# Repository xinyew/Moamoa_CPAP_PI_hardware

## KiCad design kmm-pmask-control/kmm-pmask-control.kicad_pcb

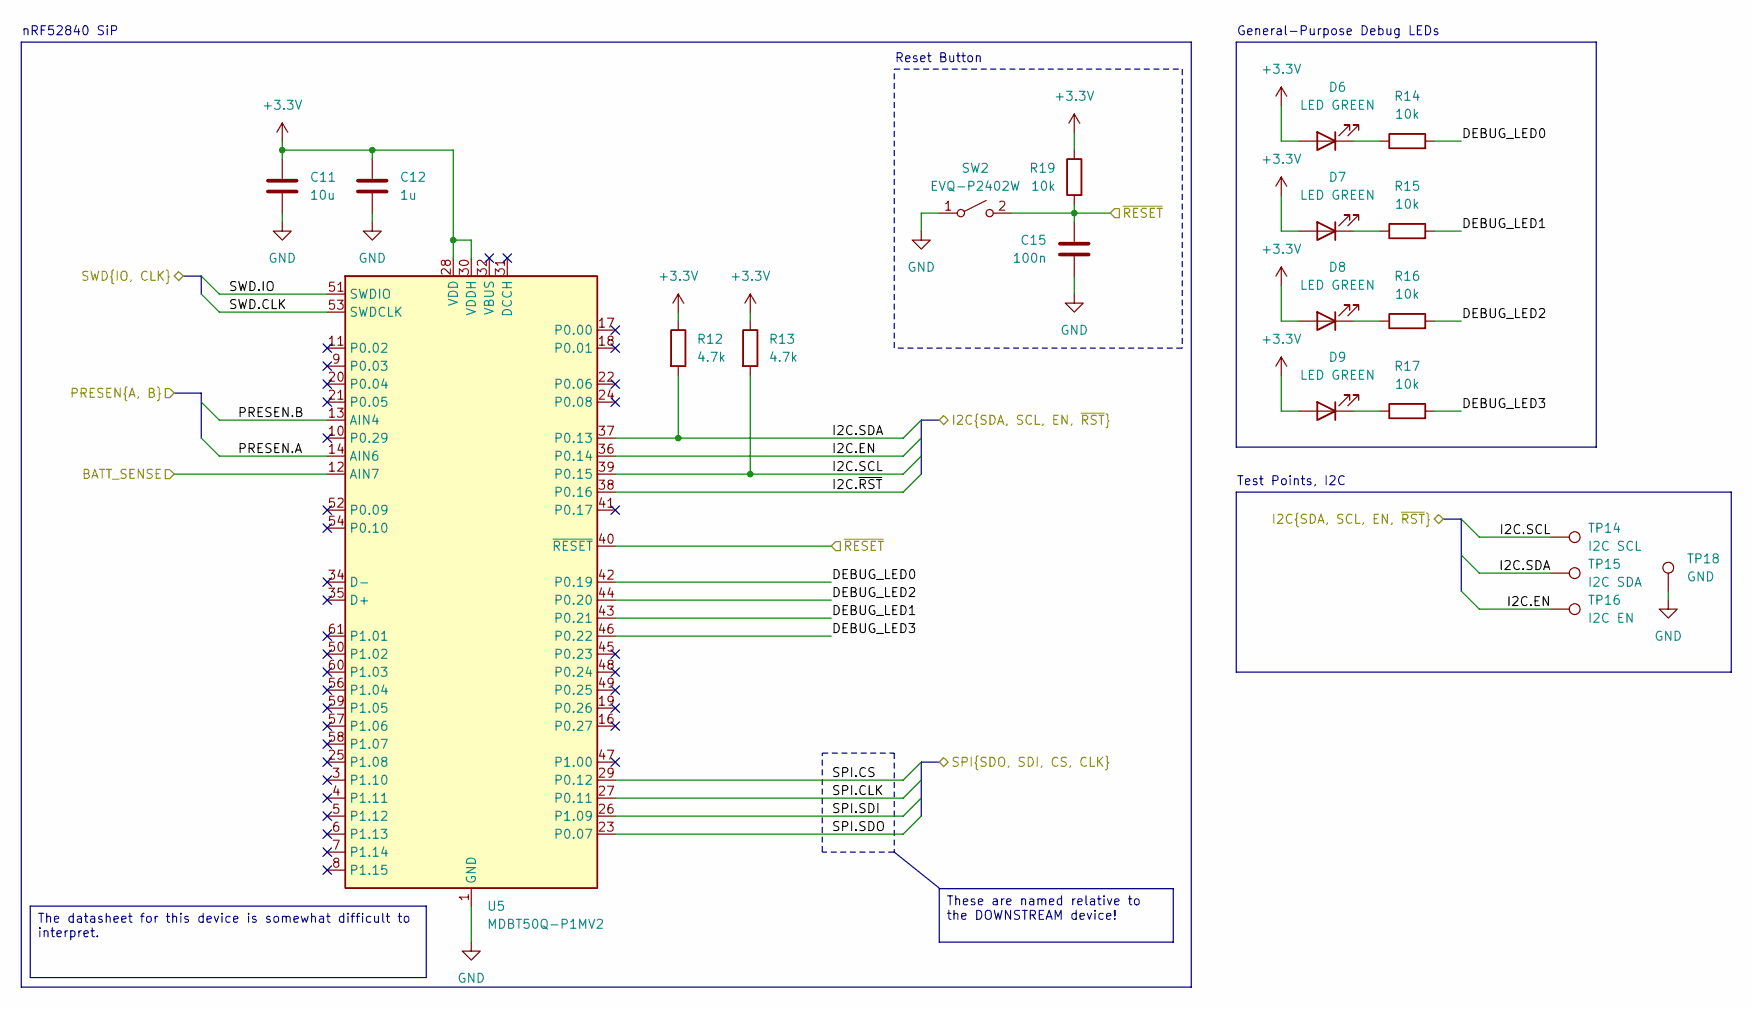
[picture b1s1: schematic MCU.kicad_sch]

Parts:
C11: 10u; C_0603_1608Metric_Pad1.08x0.95mm_HandSolder
C12: 1u; C_0402_1005Metric_Pad0.74x0.62mm_HandSolder
C15: 100n; C_0402_1005Metric_Pad0.74x0.62mm_HandSolder
D6, D7, D8, D9: LED GREEN; LED_0603_1608Metric_Pad1.05x0.95mm_HandSolder; Manufacturer P/N LTST-C190GKT
R12, R13: 4.7k; R_0402_1005Metric_Pad0.72x0.64mm_HandSolder
R14, R15, R16, R17, R19: 10k; R_0402_1005Metric_Pad0.72x0.64mm_HandSolder
SW2: EVQ-P2402W; SW_SPST_EVQP2_ShortPushTravel_H2.5mm; Manufacturer P/N EVQ-P2402W
TP14: I2C SCL; TestPoint_Pad_D1.0mm
TP15: I2C SDA; TestPoint_Pad_D1.0mm
TP16: I2C EN; TestPoint_Pad_D1.0mm
TP18: GND; TestPoint_Pad_D1.0mm
U5: MDBT50Q-P1MV2; Raytac_MDBT50Q; Manufacturer P/N MDBT50Q-P1MV2

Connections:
+3.3V: C11.1, C12.1, D6.2 (A), D7.2 (A), D8.2 (A), D9.2 (A), R12.1, R13.1, R19.1, U5.28 (VDD), U5.30 (VDDH); also elsewhere on the board
/Board Perhipherals/SPI.CLK: U5.27 (P0.11); also elsewhere on the board
/Board Perhipherals/SPI.CS: U5.29 (P0.12); also elsewhere on the board
/Board Perhipherals/SPI.SDI: U5.26 (P1.09); also elsewhere on the board
/Board Perhipherals/SPI.SDO: U5.23 (P0.07); also elsewhere on the board
/Board Perhipherals/SWD.CLK: U5.53 (SWDCLK); also elsewhere on the board
/Board Perhipherals/SWD.IO: U5.51 (SWDIO); also elsewhere on the board
/Board Perhipherals/~RESET: C15.1, R19.2, SW2.2 (B), U5.40 (~RESET); also elsewhere on the board
/MCU/BATT_SENSE: U5.12 (AIN7); also elsewhere on the board
/MCU/DEBUG_LED0: R14.2, U5.42 (P0.19)
/MCU/DEBUG_LED1: R15.2, U5.43 (P0.21)
/MCU/DEBUG_LED2: R16.2, U5.44 (P0.20)
/MCU/DEBUG_LED3: R17.2, U5.46 (P0.22)
/MCU/I2C.EN: TP16.1 (1_1), U5.36 (P0.14); also elsewhere on the board
/MCU/I2C.SCL: R13.2, TP14.1 (1_1), U5.39 (P0.15); also elsewhere on the board
/MCU/I2C.SDA: R12.2, TP15.1 (1_1), U5.37 (P0.13); also elsewhere on the board
/MCU/I2C.~RST: U5.38 (P0.16); also elsewhere on the board
/MCU/PRESEN.A: U5.14 (AIN6); also elsewhere on the board
/MCU/PRESEN.B: U5.13 (AIN4); also elsewhere on the board
GND: C11.2, C12.2, C15.2, SW2.1 (A), TP18.1 (1_1), U5.1 (GND), U5.2 (GND), U5.15 (GND), U5.33 (GND), U5.55 (GND); also elsewhere on the board
unnamed: D6.1 (K), R14.1
unnamed: D7.1 (K), R15.1
unnamed: D8.1 (K), R16.1
unnamed: D9.1 (K), R17.1

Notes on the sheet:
nRF52840 SiP
Reset Button
General-Purpose Debug LEDs
Test Points, I2C
The datasheet for this device is somewhat difficult to interpret.
These are named relative to the DOWNSTREAM device!

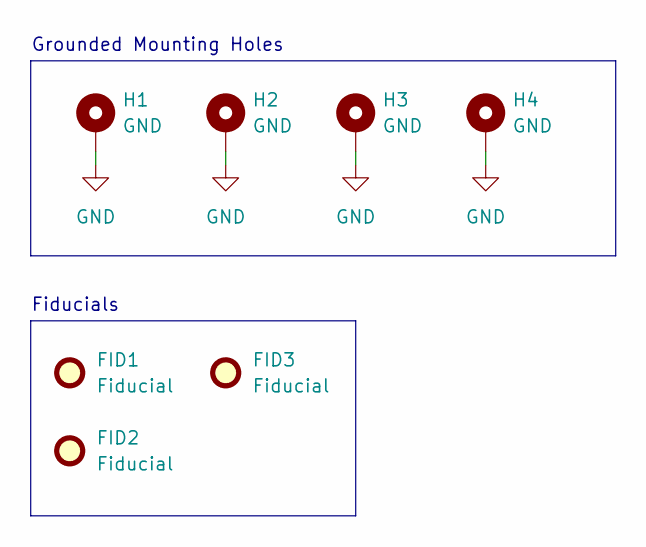
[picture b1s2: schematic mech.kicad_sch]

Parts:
FID1, FID2, FID3: Fiducial; Fiducial_1mm_Mask3mm
H1, H2, H3, H4: GND; MountingHole_3.2mm_M3_Pad

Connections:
GND: H1.1 (1_1), H2.1 (1_1), H3.1 (1_1), H4.1 (1_1); also elsewhere on the board

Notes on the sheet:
Grounded Mounting Holes
Fiducials

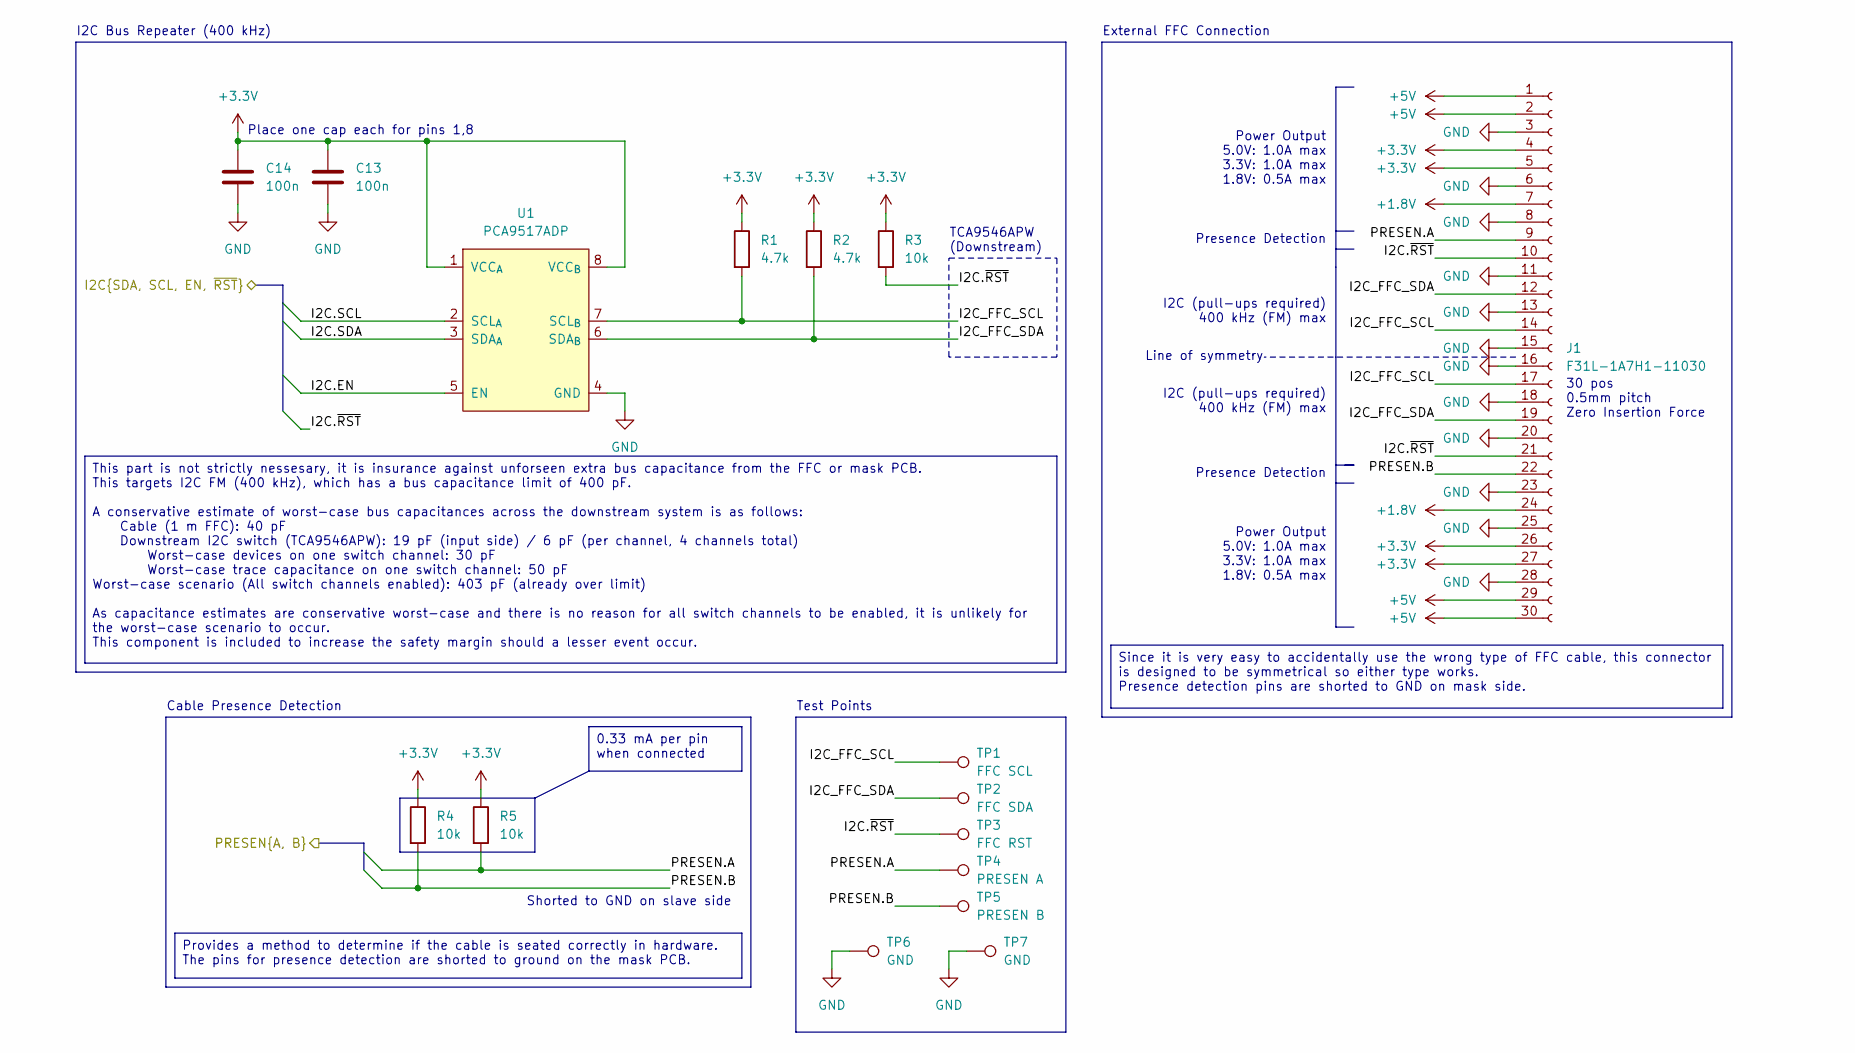
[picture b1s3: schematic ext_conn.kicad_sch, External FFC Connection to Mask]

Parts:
C13, C14: 100n; C_0402_1005Metric_Pad0.74x0.62mm_HandSolder
J1: F31L-1A7H1-11030; AMPHENOL_F31L-1A7H1-11030; Manufacturer P/N F31L-1A7H1-11030
R1, R2: 4.7k; R_0402_1005Metric_Pad0.72x0.64mm_HandSolder
R3, R4, R5: 10k; R_0402_1005Metric_Pad0.72x0.64mm_HandSolder
TP1: FFC SCL; TestPoint_Pad_D1.0mm
TP2: FFC SDA; TestPoint_Pad_D1.0mm
TP3: FFC RST; TestPoint_Pad_D1.0mm
TP4: PRESEN A; TestPoint_Pad_D1.0mm
TP5: PRESEN B; TestPoint_Pad_D1.0mm
TP6, TP7: GND; TestPoint_Pad_D1.0mm
U1: PCA9517ADP; TSSOP-8_3x3mm_P0.65mm; Manufacturer P/N PCA9517ADP,118

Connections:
+1.8V: J1.7, J1.24; also elsewhere on the board
+3.3V: C13.1, C14.1, J1.4, J1.5, J1.26, J1.27, R1.1, R2.1, R3.1, R4.1, R5.1, U1.1 (VCC_{A}), U1.8 (VCC_{B}); also elsewhere on the board
+5V: J1.1, J1.2, J1.29, J1.30; also elsewhere on the board
/MCU/I2C.EN: U1.5 (EN); also elsewhere on the board
/MCU/I2C.SCL: U1.2 (SCL_{A}); also elsewhere on the board
/MCU/I2C.SDA: U1.3 (SDA_{A}); also elsewhere on the board
/MCU/I2C.~RST: J1.10, J1.21, R3.2, TP3.1 (1_1); also elsewhere on the board
/MCU/PRESEN.A: J1.9, R5.2, TP4.1 (1_1); also elsewhere on the board
/MCU/PRESEN.B: J1.22, R4.2, TP5.1 (1_1); also elsewhere on the board
/Mask Connection/I2C_FFC_SCL: J1.14, J1.17, R1.2, TP1.1 (1_1), U1.7 (SCL_{B})
/Mask Connection/I2C_FFC_SDA: J1.12, J1.19, R2.2, TP2.1 (1_1), U1.6 (SDA_{B})
GND: C13.2, C14.2, J1.3, J1.6, J1.8, J1.11, J1.13, J1.15, J1.16, J1.18, J1.20, J1.23, J1.25, J1.28, TP6.1 (1_1), TP7.1 (1_1), U1.4 (GND); also elsewhere on the board

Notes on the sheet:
Place one cap each for pins 1,8
Line of symmetry
30 pos 0.5mm pitch Zero Insertion Force
Power Output 5.0V: 1.0A max 3.3V: 1.0A max 1.8V: 0.5A max
I2C (pull-ups required) 400 kHz (FM) max
Shorted to GND on slave side
Cable Presence Detection
External FFC Connection
Presence Detection
Test Points
TCA9546APW (Downstream)
I2C Bus Repeater (400 kHz)
Since it is very easy to accidentally use the wrong type of FFC cable, this connector is designed to be symmetrical so either type works. Presence detection pins are shorted to GND on mask side.
0.33 mA per pin when connected
This part is not strictly nessesary, it is insurance against unforseen extra bus capacitance from the FFC or mask PCB. This targets I2C FM (400 kHz), which has a bus capacitance limit of 400 pF. A conservative estimate of worst-case bus capacitances across the downstream system is as follows: Cable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
Provides a method to determine if the cable is seated correctly in hardware. The pins for presence detection are shorted to ground on the mask PCB.

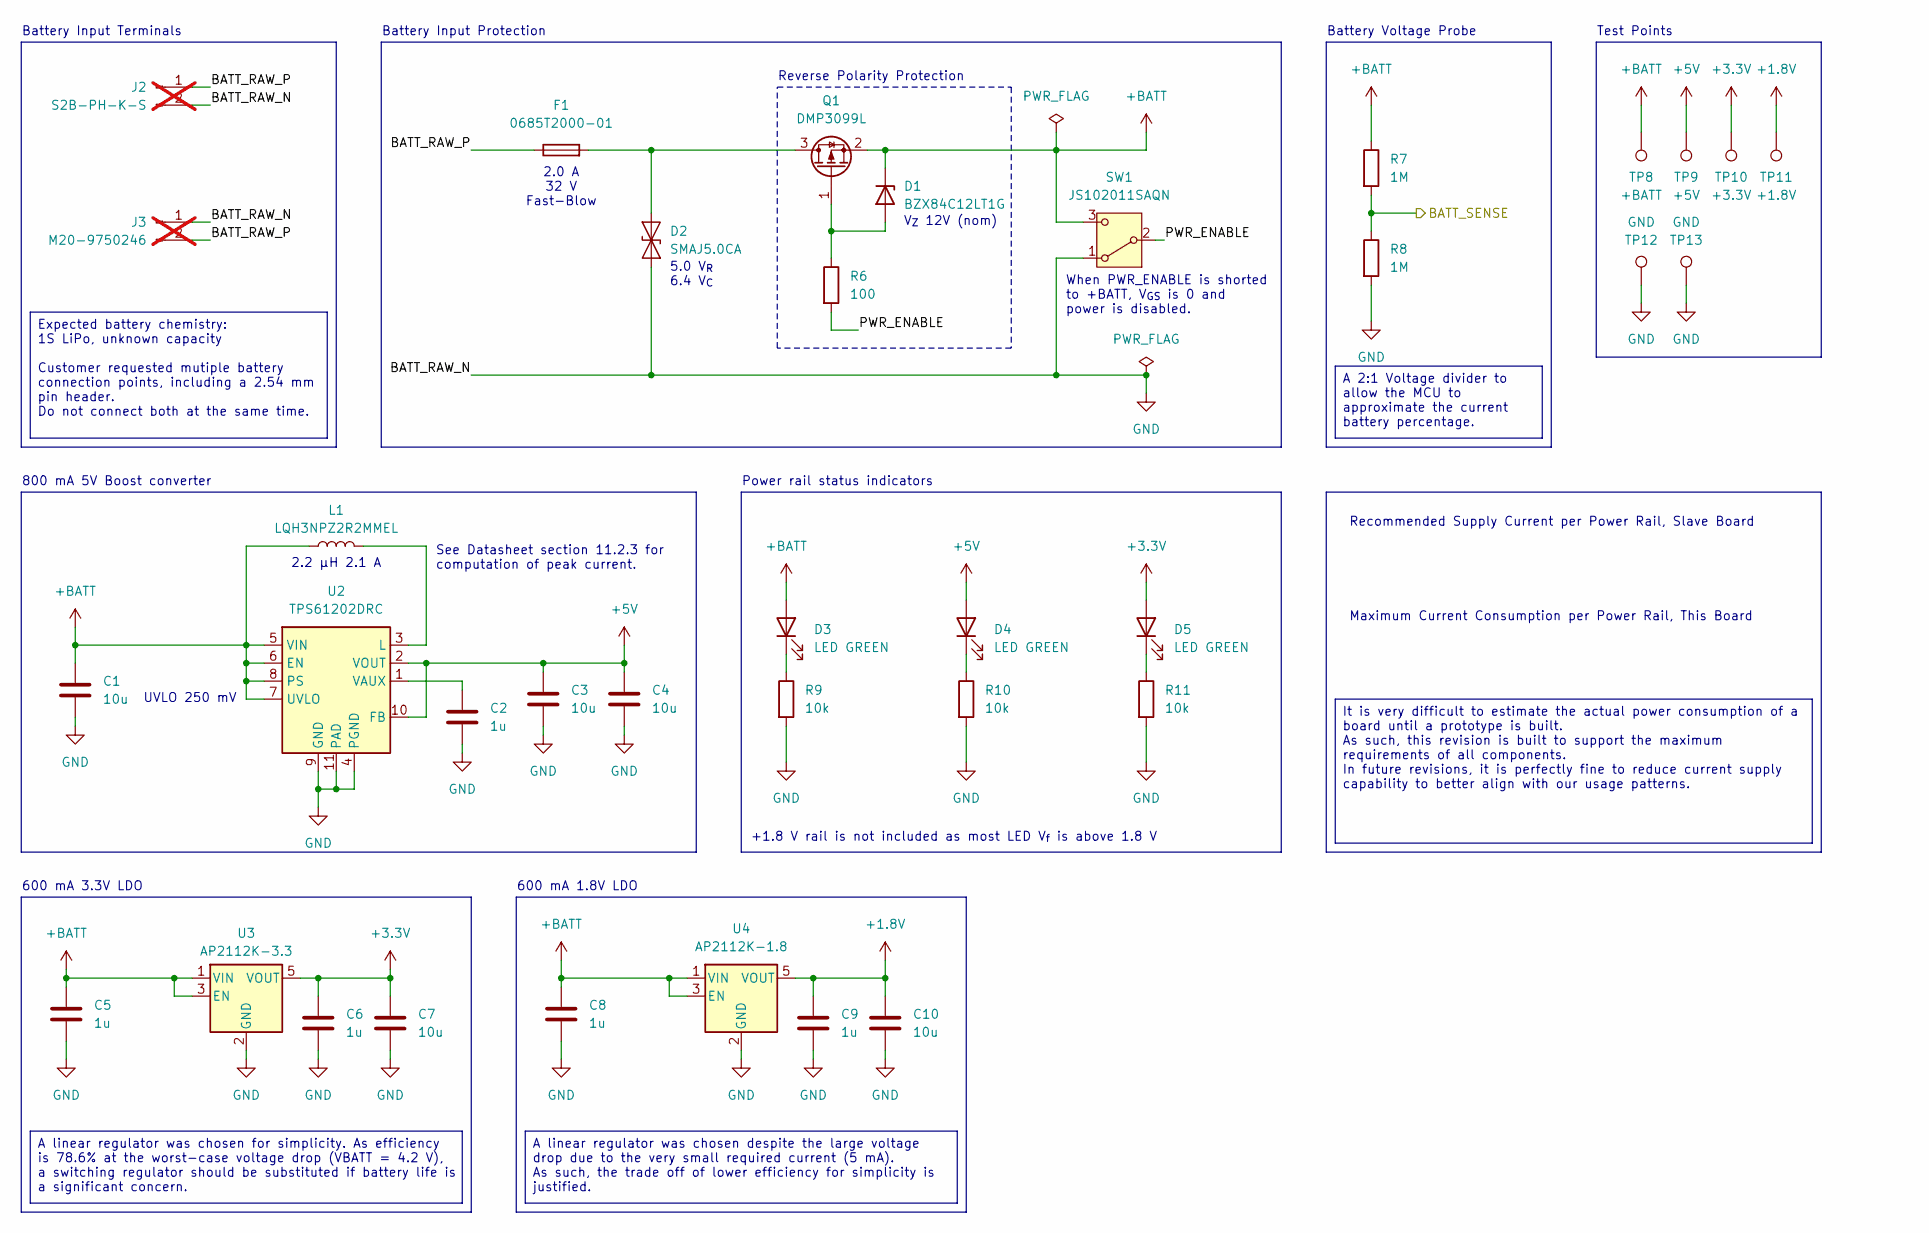
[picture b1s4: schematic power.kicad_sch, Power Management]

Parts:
C1, C3, C4, C7, C10: 10u; C_0603_1608Metric_Pad1.08x0.95mm_HandSolder
C2, C5, C6, C8, C9: 1u; C_0402_1005Metric_Pad0.74x0.62mm_HandSolder
D1: BZX84C12LT1G; SOT-23; Manufacturer P/N BZX84C12LT1G
D2: SMAJ5.0CA; D_SMA; Manufacturer P/N SMAJ5.0CA
D3, D4, D5: LED GREEN; LED_0603_1608Metric_Pad1.05x0.95mm_HandSolder; Manufacturer P/N LTST-C190GKT
F1: 0685T2000-01; Fuse_1206_3216Metric_Pad1.42x1.75mm_HandSolder; Manufacturer P/N 0685T2000-01
J2: S2B-PH-K-S; JST_PH_S2B-PH-K_1x02_P2.00mm_Horizontal; Manufacturer P/N S2B-PH-K-S; not fitted
J3: M20-9750246; PinHeader_1x02_P2.54mm_Horizontal; Manufacturer P/N M20-9750246; not fitted
L1: LQH3NPZ2R2MMEL; IND_LQH3NPZ2R2MMEL; Manufacturer P/N LQH3NPZ2R2MMEL
Q1: DMP3099L; SOT-23; Manufacturer P/N DMP3099L-13
R6: 100; R_0402_1005Metric_Pad0.72x0.64mm_HandSolder
R7, R8: 1M; R_0402_1005Metric_Pad0.72x0.64mm_HandSolder
R9, R10, R11: 10k; R_0402_1005Metric_Pad0.72x0.64mm_HandSolder
SW1: JS102011SAQN; SW_SPDT_CK_JS102011SAQN; Manufacturer P/N JS102011SAQN
TP8: +BATT; TestPoint_Pad_D1.0mm
TP9: +5V; TestPoint_Pad_D1.0mm
TP10: +3.3V; TestPoint_Pad_D1.0mm
TP11: +1.8V; TestPoint_Pad_D1.0mm
TP12, TP13: GND; TestPoint_Pad_D1.0mm
U2: TPS61202DRC; Texas_S-PVSON-N10_ThermalVias; Manufacturer P/N TPS61202DRCR
U3: AP2112K-3.3; SOT-23-5; Manufacturer P/N AP2112K-3.3TRG1
U4: AP2112K-1.8; SOT-23-5; Manufacturer P/N AP2112K-1.8TRG1

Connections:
+1.8V: C9.1, C10.1, TP11.1 (1_1), U4.5 (VOUT); also elsewhere on the board
+3.3V: C6.1, C7.1, D5.2 (A), TP10.1 (1_1), U3.5 (VOUT); also elsewhere on the board
+5V: C3.1, C4.1, D4.2 (A), TP9.1 (1_1), U2.2 (VOUT), U2.10 (FB); also elsewhere on the board
+BATT: C1.1, C5.1, C8.1, D1.3 (K), D3.2 (A), L1.1, Q1.2 (S), R7.1, SW1.3 (C), TP8.1 (1_1), U2.5 (VIN), U2.6 (EN), U2.7 (UVLO), U2.8 (PS), U3.1 (VIN), U3.3 (EN), U4.1 (VIN), U4.3 (EN)
/MCU/BATT_SENSE: R7.2, R8.1; also elsewhere on the board
/Power/BATT_RAW_P: F1.1, J2.1, J3.2
/Power/PWR_ENABLE: R6.2, SW1.2 (B)
GND: C1.2, C2.2, C3.2, C4.2, C5.2, C6.2, C7.2, C8.2, C9.2, C10.2, D2.1 (A1), J2.2, J3.1, R8.2, R9.2, R10.2, R11.2, SW1.1 (A), TP12.1 (1_1), TP13.1 (1_1), U2.4 (PGND), U2.9 (GND), U2.11 (PAD), U3.2 (GND), U4.2 (GND); also elsewhere on the board
unnamed: D1.1 (A), Q1.1 (G), R6.1
unnamed: D2.2 (A2), F1.2, Q1.3 (D)
unnamed: D3.1 (K), R9.1
unnamed: D4.1 (K), R10.1
unnamed: D5.1 (K), R11.1
unnamed: L1.2, U2.3 (L)
unnamed: C2.1, U2.1 (VAUX)

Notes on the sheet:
Battery Voltage Probe
Maximum Current Consumption per Power Rail, This Board
V_{Z} 12V (nom)
Power rail status indicators
600 mA 3.3V LDO
When PWR_ENABLE is shorted to +BATT, V_{GS} is 0 and power is disabled.
Reverse Polarity Protection
Test Points
600 mA 1.8V LDO
800 mA 5V Boost converter
+1.8 V rail is not included as most LED V_{f} is above 1.8 V
Battery Input Protection
Battery Input Terminals
2.0 A 32 V Fast-Blow
5.0 V_{R} 6.4 V_{C}
Recommended Supply Current per Power Rail, Slave Board
UVLO 250 mV
See Datasheet section 11.2.3 for computation of peak current.
2.2 µH 2.1 A
A linear regulator was chosen for simplicity. As efficiency is 78.6% at the worst-case voltage drop (VBATT = 4.2 V), a switching regulator should be substituted if battery life is a significant concern.
Expected battery chemistry: 1S LiPo, unknown capacity Customer requested mutiple battery connection points, including a 2.54 mm pin header. Do not connect both at the same time.
It is very difficult to estimate the actual power consumption of a board until a prototype is built. As such, this revision is built to support the maximum requirements of all components. In future revisions, it is perfectly fine to reduce current supply capability to better align with our usage pa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
A 2:1 Voltage divider to allow the MCU to approximate the current battery percentage.
A linear regulator was chosen despite the large voltage drop due to the very small required current (5 mA). As such, the trade off of lower efficiency for simplicity is justified.

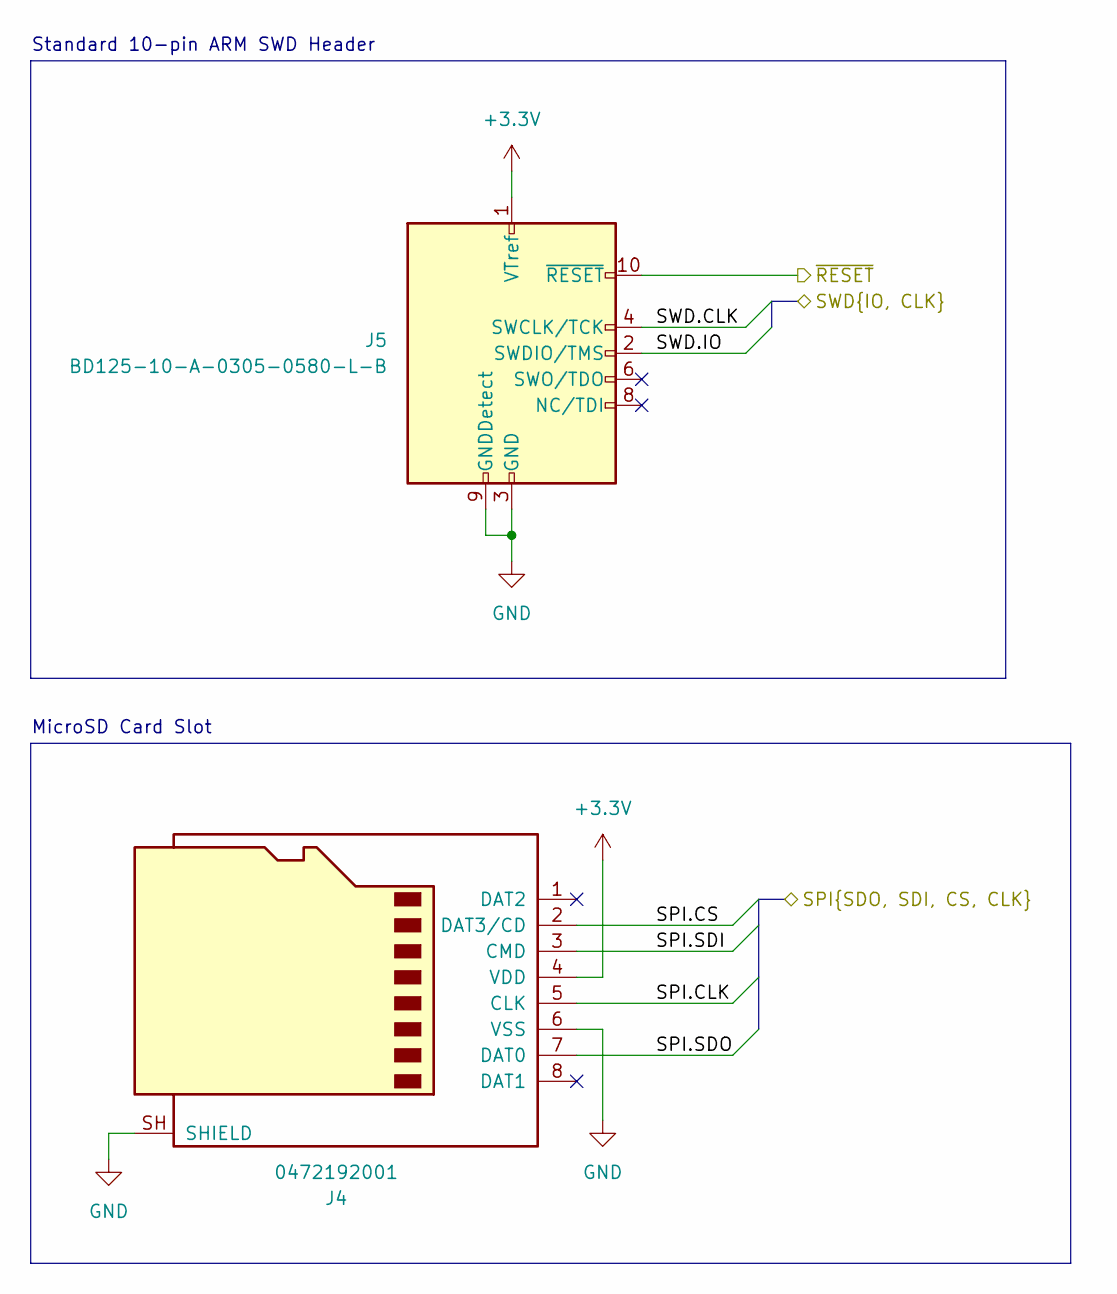
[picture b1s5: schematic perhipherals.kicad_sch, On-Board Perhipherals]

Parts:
J4: 0472192001; microSD_HC_Molex_47219-2001; Manufacturer P/N 0472192001
J5: BD125-10-A-0305-0580-L-B; PinHeader_2x05_P1.27mm_Vertical_SMD; Manufacturer P/N BD125-10-A-0305-0580-L-B

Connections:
+3.3V: J4.4 (VDD), J5.1 (VTref); also elsewhere on the board
/Board Perhipherals/SPI.CLK: J4.5 (CLK); also elsewhere on the board
/Board Perhipherals/SPI.CS: J4.2 (DAT3/CD); also elsewhere on the board
/Board Perhipherals/SPI.SDI: J4.3 (CMD); also elsewhere on the board
/Board Perhipherals/SPI.SDO: J4.7 (DAT0); also elsewhere on the board
/Board Perhipherals/SWD.CLK: J5.4 (SWCLK/TCK); also elsewhere on the board
/Board Perhipherals/SWD.IO: J5.2 (SWDIO/TMS); also elsewhere on the board
/Board Perhipherals/~RESET: J5.10 (~RESET); also elsewhere on the board
GND: J4.6 (VSS), J4.SH (SHIELD), J5.3 (GND), J5.5 (GND), J5.9 (GNDDetect); also elsewhere on the board

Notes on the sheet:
Standard 10-pin ARM SWD Header
MicroSD Card Slot

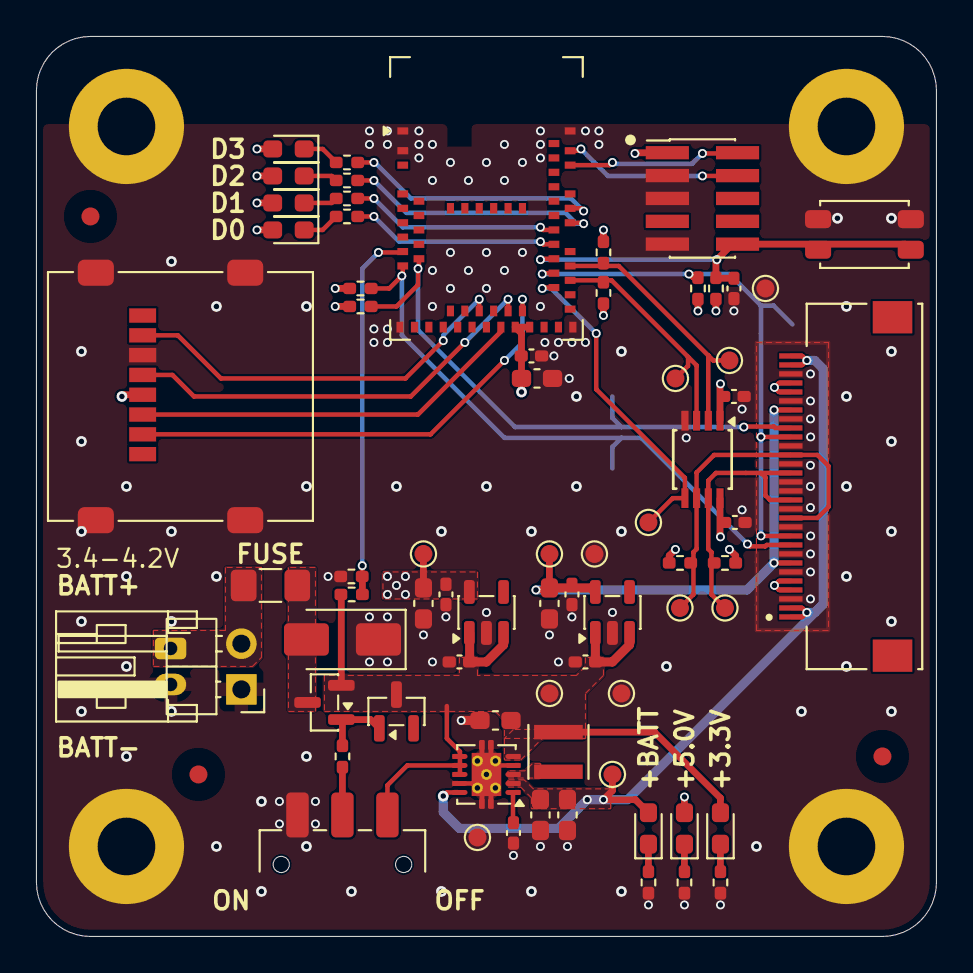
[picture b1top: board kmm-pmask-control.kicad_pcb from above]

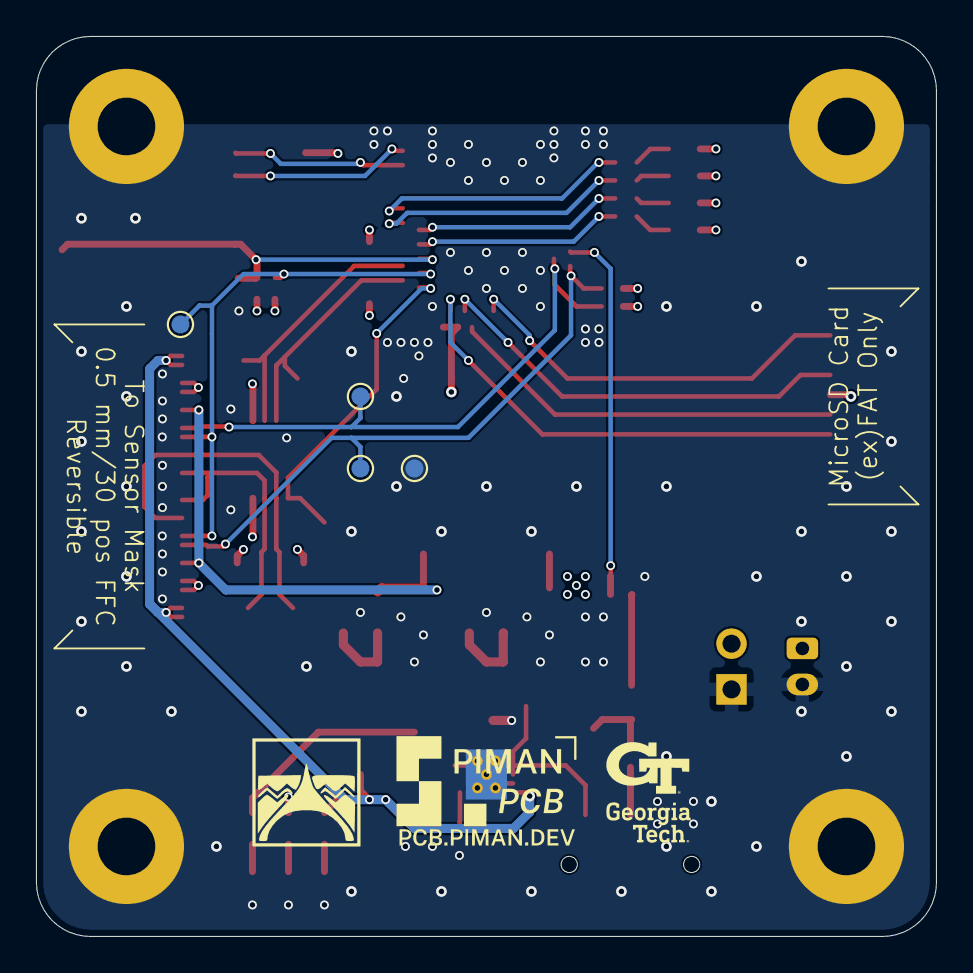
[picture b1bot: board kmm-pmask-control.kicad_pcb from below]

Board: 4 copper layers, 50.0 x 50.0 mm, 81 parts (4 on the bottom side), 38 nets.

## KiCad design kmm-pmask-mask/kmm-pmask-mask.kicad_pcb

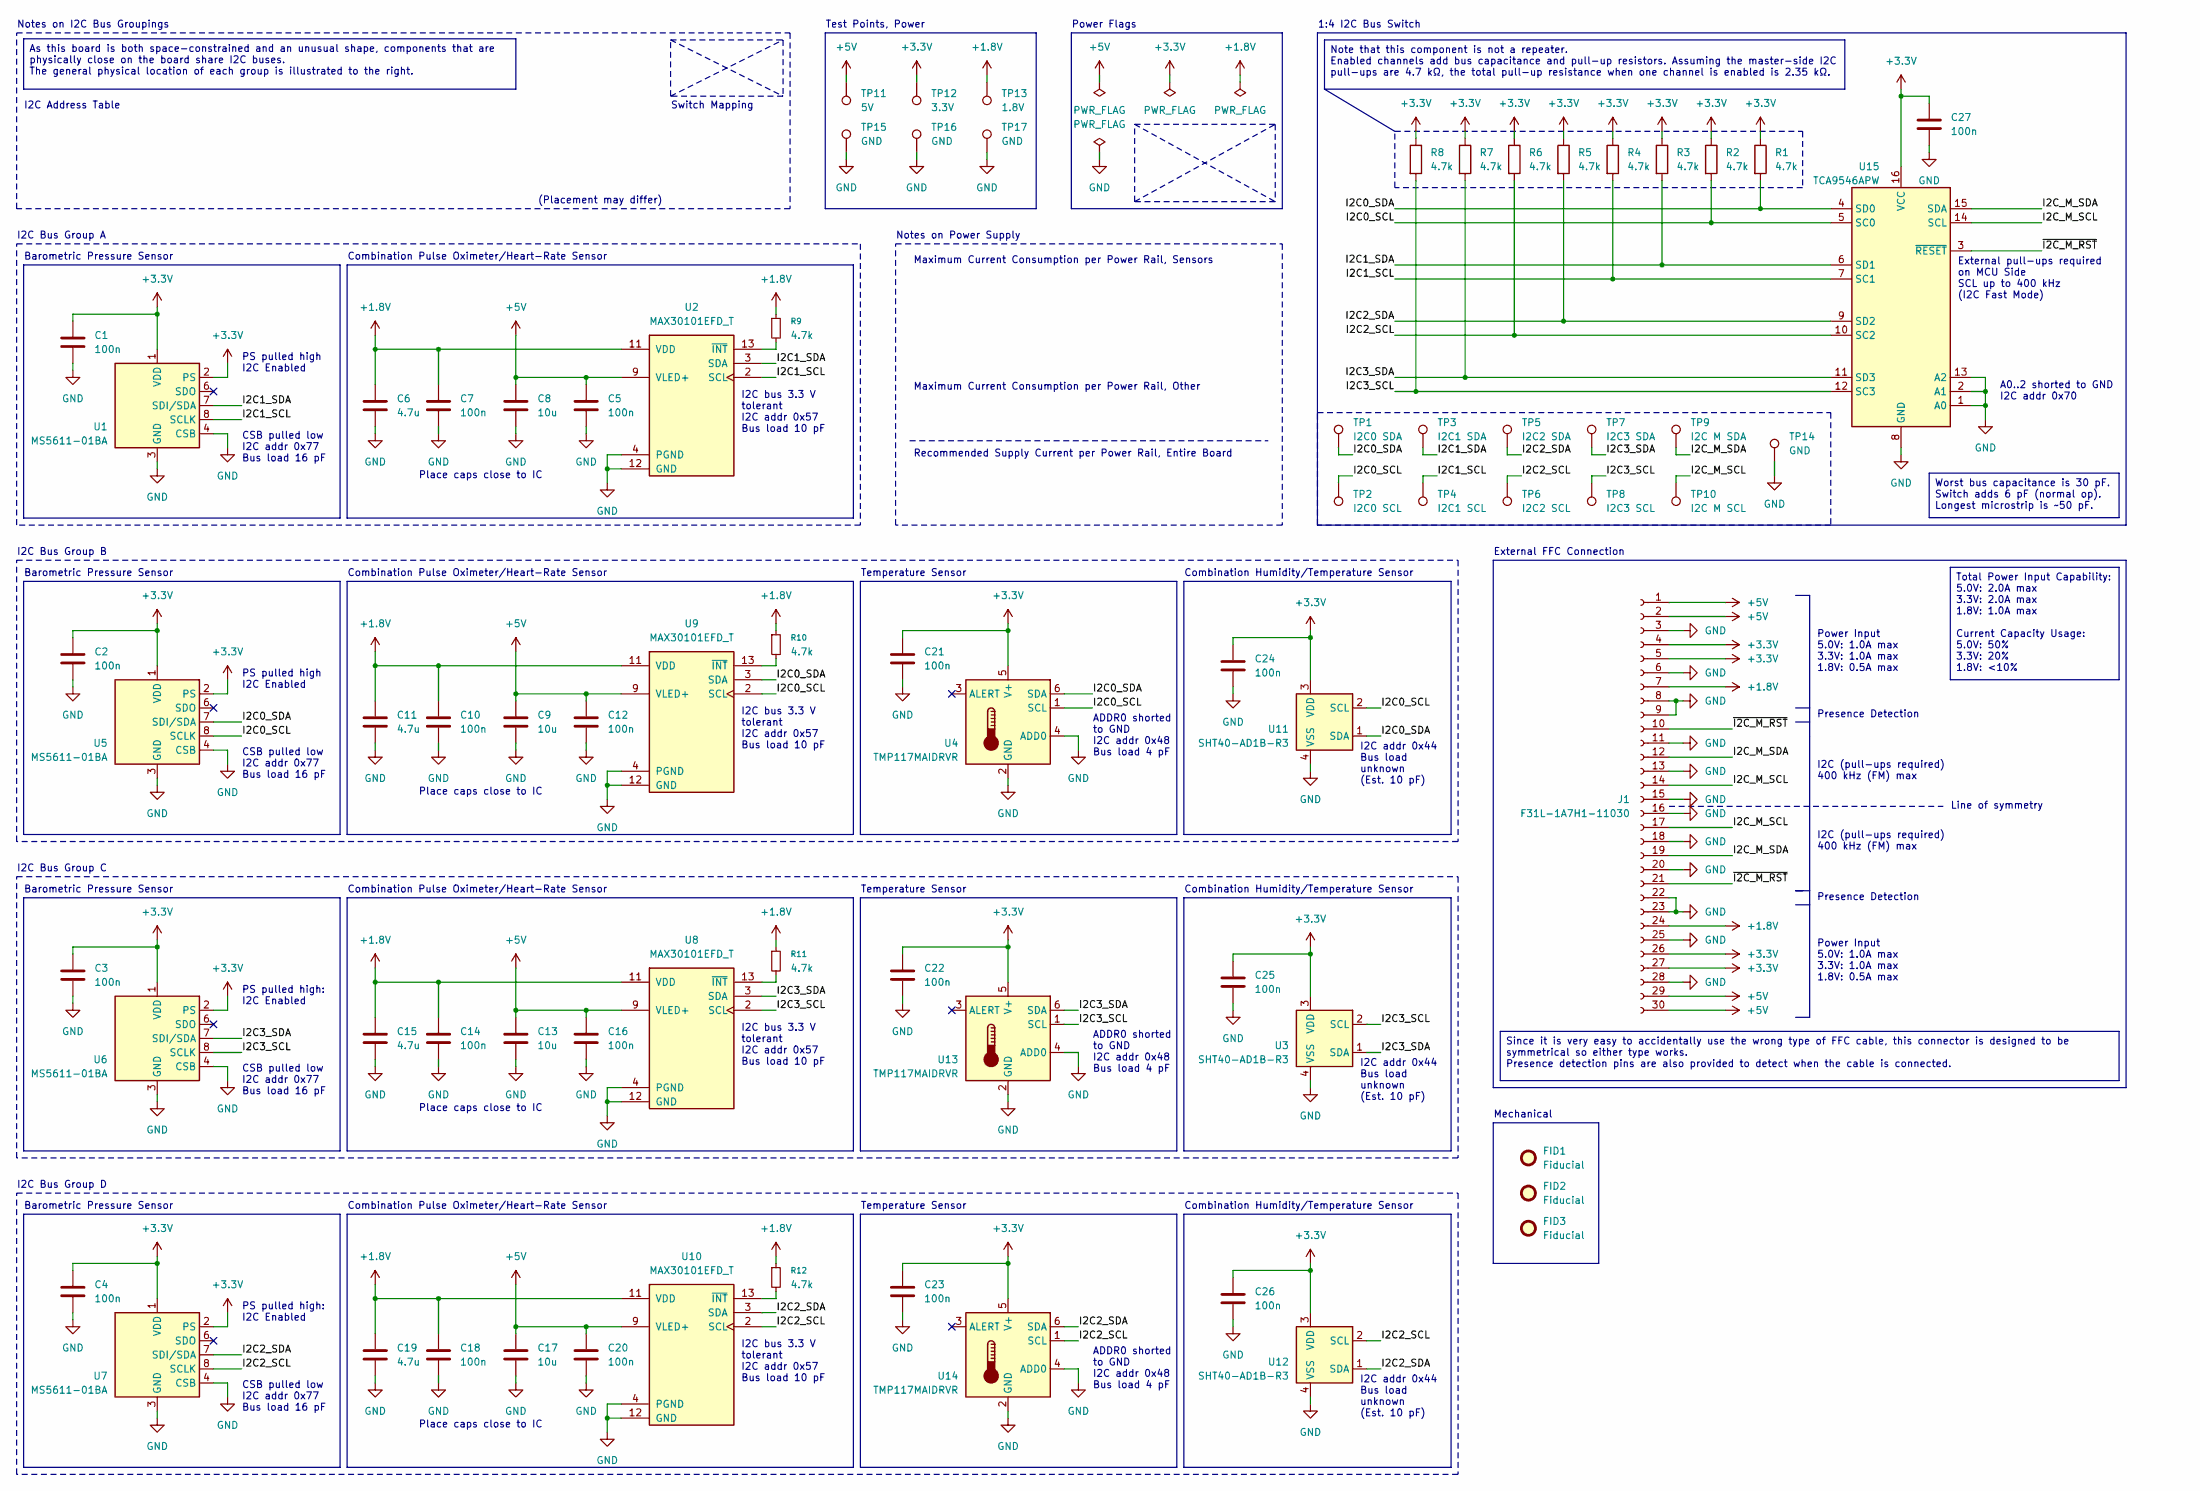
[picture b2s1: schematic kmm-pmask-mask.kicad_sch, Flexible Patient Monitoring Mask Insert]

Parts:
C1, C2, C3, C4, C5, C7, C10, C12, C14, C16, C18, C20, C21, C22, C23, C24, C25, C26, C27: 100n; C_0201_0603Metric_Pad0.64x0.40mm_HandSolder
C6, C11, C15, C19: 4.7u; C_0402_1005Metric_Pad0.74x0.62mm_HandSolder
C8, C9, C13, C17: 10u; C_0402_1005Metric_Pad0.74x0.62mm_HandSolder
FID1, FID2, FID3: Fiducial; Fiducial_1mm_Mask3mm
J1: F31L-1A7H1-11030; AMPHENOL_F31L-1A7H1-11030; Manufacturer P/N F31L-1A7H1-11030
R1, R2, R3, R4, R5, R6, R7, R8, R9, R10, R11, R12: 4.7k; R_0201_0603Metric_Pad0.64x0.40mm_HandSolder
TP1: I2C0 SDA; TestPoint_Pad_D1.0mm
TP2: I2C0 SCL; TestPoint_Pad_D1.0mm
TP3: I2C1 SDA; TestPoint_Pad_D1.0mm
TP4: I2C1 SCL; TestPoint_Pad_D1.0mm
TP5: I2C2 SDA; TestPoint_Pad_D1.0mm
TP6: I2C2 SCL; TestPoint_Pad_D1.0mm
TP7: I2C3 SDA; TestPoint_Pad_D1.0mm
TP8: I2C3 SCL; TestPoint_Pad_D1.0mm
TP9: I2C M SDA; TestPoint_Pad_D1.0mm
TP10: I2C M SCL; TestPoint_Pad_D1.0mm
TP11: 5V; TestPoint_Pad_D1.0mm
TP12: 3.3V; TestPoint_Pad_D1.0mm
TP13: 1.8V; TestPoint_Pad_D1.0mm
TP14, TP15, TP16, TP17: GND; TestPoint_Pad_D1.0mm
U1, U5, U6, U7: MS5611-01BA; LGA-8_3x5mm_P1.25mm; Manufacturer P/N MS561101BA03-50
U2, U8, U9, U10: MAX30101EFD_T; Manufacturer P/N MAX30101EFD+T
U3, U11, U12: SHT40-AD1B-R3; Sensirion_DFN-4_1.5x1.5mm_P0.8mm_SHT4x_NoCentralPad; Manufacturer P/N SHT40-AD1B-R3
U4, U13, U14: TMP117MAIDRVR; WSON-6-1EP_2x2mm_P0.65mm_EP1x1.6mm; Manufacturer P/N TMP117MAIDRVR
U15: TCA9546APW; TSSOP-16_4.4x5mm_P0.65mm

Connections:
+1.8V: C6.1, C7.1, C10.1, C11.1, C14.1, C15.1, C18.1, C19.1, J1.7, J1.24, R9.1, R10.1, R11.1, R12.1, TP13.1 (1_1), U2.11 (VDD), U8.11 (VDD), U9.11 (VDD), U10.11 (VDD)
+3.3V: C1.1, C2.1, C3.1, C4.1, C21.1, C22.1, C23.1, C24.1, C25.1, C26.1, C27.1, J1.4, J1.5, J1.26, J1.27, R1.1, R2.1, R3.1, R4.1, R5.1, R6.1, R7.1, R8.1, TP12.1 (1_1), U1.1 (VDD), U1.2 (PS), U3.3 (VDD), U4.5 (V+), U5.1 (VDD), U5.2 (PS), U6.1 (VDD), U6.2 (PS), U7.1 (VDD), U7.2 (PS), U11.3 (VDD), U12.3 (VDD), U13.5 (V+), U14.5 (V+), U15.16 (VCC)
+5V: C5.1, C8.1, C9.1, C12.1, C13.1, C16.1, C17.1, C20.1, J1.1, J1.2, J1.29, J1.30, TP11.1 (1_1), U2.9 (VLED+), U2.10 (VLED+), U8.9 (VLED+), U8.10 (VLED+), U9.9 (VLED+), U9.10 (VLED+), U10.9 (VLED+), U10.10 (VLED+)
/I2C0_SCL: R2.2, TP2.1 (1_1), U4.1 (SCL), U5.8 (SCLK), U9.2 (SCL), U11.2 (SCL), U15.5 (SC0)
/I2C0_SDA: R1.2, TP1.1 (1_1), U4.6 (SDA), U5.7 (SDI/SDA), U9.3 (SDA), U11.1 (SDA), U15.4 (SD0)
/I2C1_SCL: R4.2, TP4.1 (1_1), U1.8 (SCLK), U2.2 (SCL), U15.7 (SC1)
/I2C1_SDA: R3.2, TP3.1 (1_1), U1.7 (SDI/SDA), U2.3 (SDA), U15.6 (SD1)
/I2C2_SCL: R6.2, TP6.1 (1_1), U7.8 (SCLK), U10.2 (SCL), U12.2 (SCL), U14.1 (SCL), U15.10 (SC2)
/I2C2_SDA: R5.2, TP5.1 (1_1), U7.7 (SDI/SDA), U10.3 (SDA), U12.1 (SDA), U14.6 (SDA), U15.9 (SD2)
/I2C3_SCL: R8.2, TP8.1 (1_1), U3.2 (SCL), U6.8 (SCLK), U8.2 (SCL), U13.1 (SCL), U15.12 (SC3)
/I2C3_SDA: R7.2, TP7.1 (1_1), U3.1 (SDA), U6.7 (SDI/SDA), U8.3 (SDA), U13.6 (SDA), U15.11 (SD3)
/I2C_M_SCL: J1.14, J1.17, TP10.1 (1_1), U15.14 (SCL)
/I2C_M_SDA: J1.12, J1.19, TP9.1 (1_1), U15.15 (SDA)
/~I2C_M_RST: J1.10, J1.21, U15.3 (~RESET)
GND: C1.2, C2.2, C3.2, C4.2, C5.2, C6.2, C7.2, C8.2, C9.2, C10.2, C11.2, C12.2, C13.2, C14.2, C15.2, C16.2, C17.2, C18.2, C19.2, C20.2, C21.2, C22.2, C23.2, C24.2, C25.2, C26.2, C27.2, J1.3, J1.6, J1.8, J1.9, J1.11, J1.13, J1.15, J1.16, J1.18, J1.20, J1.22, J1.23, J1.25, J1.28, TP14.1 (1_1), TP15.1 (1_1), TP16.1 (1_1), TP17.1 (1_1), U1.3 (GND), U1.4 (CSB), U1.5 (CSB), U2.4 (PGND), U2.12 (GND), U3.4 (VSS), U4.2 (GND), U4.4 (ADD0), U5.3 (GND), U5.4 (CSB), U5.5 (CSB), U6.3 (GND), U6.4 (CSB), U6.5 (CSB), U7.3 (GND), U7.4 (CSB), U7.5 (CSB), U8.4 (PGND), U8.12 (GND), U9.4 (PGND), U9.12 (GND), U10.4 (PGND), U10.12 (GND), U11.4 (VSS), U12.4 (VSS), U13.2 (GND), U13.4 (ADD0), U14.2 (GND), U14.4 (ADD0), U15.1 (A0), U15.2 (A1), U15.8 (GND), U15.13 (A2)
unnamed: R9.2, U2.13 (~INT)
unnamed: R11.2, U8.13 (~INT)
unnamed: R10.2, U9.13 (~INT)
unnamed: R12.2, U10.13 (~INT)

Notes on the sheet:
Switch Mapping
I2C (pull-ups required) 400 kHz (FM) max
1:4 I2C Bus Switch
Barometric Pressure Sensor
CSB pulled low I2C addr 0x77 Bus load 16 pF
PS pulled high I2C Enabled
Test Points, Power
ADDR0 shorted to GND I2C addr 0x48 Bus load 4 pF
Temperature Sensor
I2C bus 3.3 V tolerant I2C addr 0x57 Bus load 10 pF
(Placement may differ)
Presence Detection
Notes on Power Supply
I2C Bus Group C
Place caps close to IC
Combination Pulse Oximeter/Heart-Rate Sensor
External FFC Connection
Power Input 5.0V: 1.0A max 3.3V: 1.0A max 1.8V: 0.5A max
Maximum Current Consumption per Power Rail, Sensors
I2C Bus Group D
I2C Bus Group B
I2C addr 0x44 Bus load unknown (Est. 10 pF)
PS pulled high: I2C Enabled
Power Flags
Maximum Current Consumption per Power Rail, Other
Combination Humidity/Temperature Sensor
Line of symmetry
Recommended Supply Current per Power Rail, Entire Board
I2C Bus Group A
Mechanical
External pull-ups required on MCU Side SCL up to 400 kHz (I2C Fast Mode)
Notes on I2C Bus Groupings
I2C Address Table
A0..2 shorted to GND I2C addr 0x70
Since it is very easy to accidentally use the wrong type of FFC cable, this connector is designed to be symmetrical so either type works. Presence detection pins are also provided to detect when the cable is connected.
As this board is both space-constrained and an unusual shape, components that are physically close on the board share I2C buses. The general physical location of each group is illustrated to the right.
Note that this component is not a repeater. Enabled channels add bus capacitance and pull-up resistors. Assuming the master-side I2C pull-ups are 4.7 kΩ, the total pull-up resistance when one channel is enabled is 2.35 kΩ.
Total Power Input Capability: 5.0V: 2.0A max 3.3V: 2.0A max 1.8V: 1.0A max Current Capacity Usage: 5.0V: 50% 3.3V: 20% 1.8V: <10%
Worst bus capacitance is 30 pF. Switch adds 6 pF (normal op). Longest microstrip is ~50 pF.
